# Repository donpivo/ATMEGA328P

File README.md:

Project description:
https://retronics.no/2023/04/09/diy-atmega328p-au-bootloader-burner/
https://retronics.no/2023/04/26/dyi-a-mini-arduino-which-can-power-your-peripherals/

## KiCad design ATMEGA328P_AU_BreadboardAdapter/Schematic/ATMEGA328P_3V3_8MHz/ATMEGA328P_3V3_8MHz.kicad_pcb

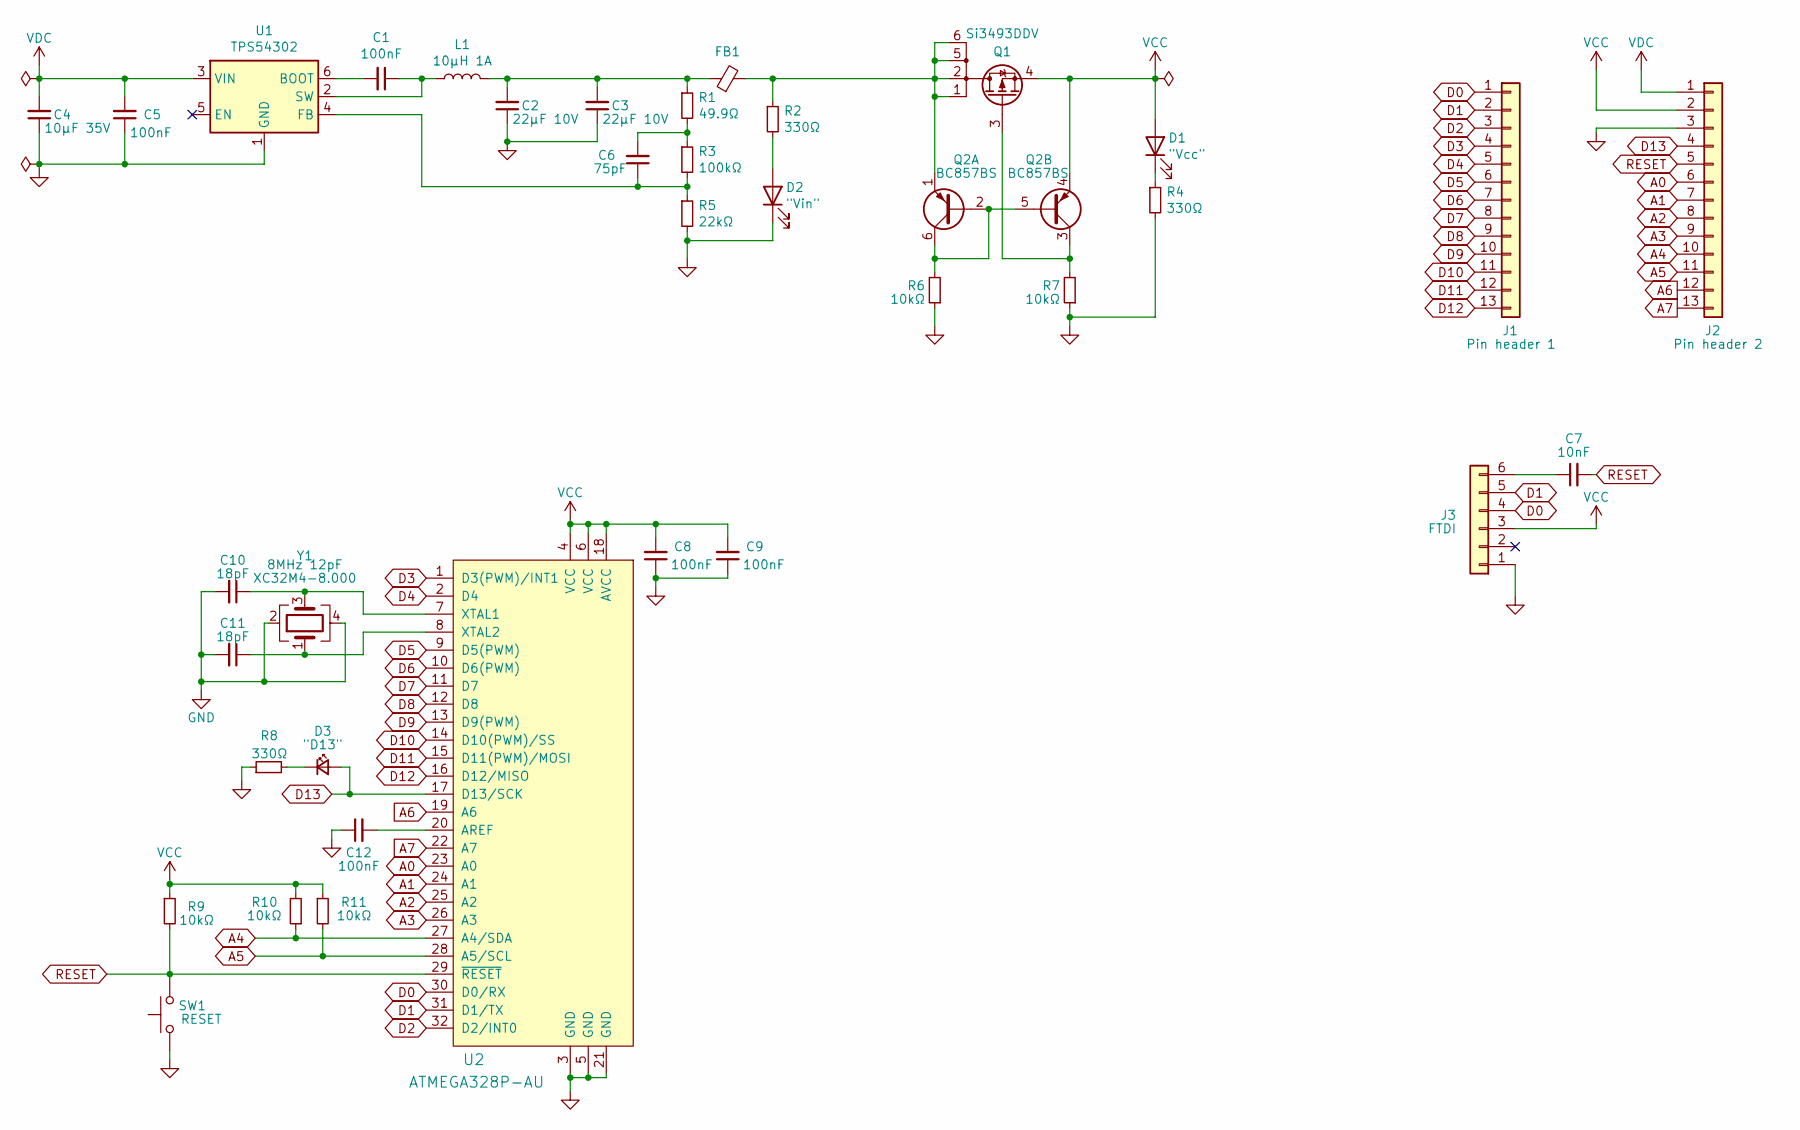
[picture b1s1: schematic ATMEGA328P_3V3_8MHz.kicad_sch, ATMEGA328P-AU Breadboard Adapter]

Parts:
C1, C5, C8, C9, C12: 100nF; C_0603_1608Metric_Pad1.08x0.95mm_HandSolder
C2, C3: 22µF 10V; C_0603_1608Metric_Pad1.08x0.95mm_HandSolder
C4: 10µF 35V; C_0603_1608Metric_Pad1.08x0.95mm_HandSolder
C6: 75pF; C_0603_1608Metric_Pad1.08x0.95mm_HandSolder
C7: 10nF; C_0603_1608Metric_Pad1.08x0.95mm_HandSolder
C10, C11: 18pF; C_0603_1608Metric_Pad1.08x0.95mm_HandSolder
D1: "Vcc"; LED_0603_1608Metric_Pad1.05x0.95mm_HandSolder
D2: "Vin"; LED_0603_1608Metric_Pad1.05x0.95mm_HandSolder
D3: "D13"; LED_0603_1608Metric_Pad1.05x0.95mm_HandSolder
FB1: FerriteBead_Small; L_0603_1608Metric_Pad1.05x0.95mm_HandSolder
J1: Pin header 1; PinHeader_1x13_P2.54mm_Vertical
J2: Pin header 2; PinHeader_1x13_P2.54mm_Vertical
J3: FTDI; PinHeader_1x06_P2.54mm_Vertical
L1: 10µH 1A; L_Taiyo-Yuden_NR-20xx_HandSoldering
Q1: Si3493DDV; SOT95P280X100-6N
Q2: BC857BS; SOT-363_SC-70-6-Handsoldering
R1: 49.9Ω; R_0603_1608Metric_Pad0.98x0.95mm_HandSolder
R2, R4, R8: 330Ω; R_0603_1608Metric_Pad0.98x0.95mm_HandSolder
R3: 100kΩ; R_0603_1608Metric_Pad0.98x0.95mm_HandSolder
R5: 22kΩ; R_0603_1608Metric_Pad0.98x0.95mm_HandSolder
R6, R7, R9, R10, R11: 10kΩ; R_0603_1608Metric_Pad0.98x0.95mm_HandSolder
SW1: RESET; Tactile_sw_SMD_side_01
U1: TPS54302; SOT-23-6_Handsoldering
U2: ATMEGA328P-AU; TQFP-32_7x7mm
Y1: 8MHz 12pF; Crystal_SMD_SeikoEpson_TSX3225-4Pin_3.2x2.5mm_HandSoldering

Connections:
A0: J2.6, U2.23 (A0)
A1: J2.7, U2.24 (A1)
A2: J2.8, U2.25 (A2)
A3: J2.9, U2.26 (A3)
A4: J2.10, R10.1, U2.27 (A4/SDA)
A5: J2.11, R11.2, U2.28 (A5/SCL)
A6: J2.12, U2.19 (A6)
A7: J2.13, U2.22 (A7)
D0: J1.1, J3.4, U2.30 (D0/RX)
D1: J1.2, J3.5, U2.31 (D1/TX)
D2: J1.3, U2.32 (D2/INT0)
D3: J1.4, U2.1 (D3(PWM)/INT1)
D4: J1.5, U2.2 (D4)
D5: J1.6, U2.9 (D5(PWM))
D6: J1.7, U2.10 (D6(PWM))
D7: J1.8, U2.11 (D7)
D8: J1.9, U2.12 (D8)
D9: J1.10, U2.13 (D9(PWM))
D10: J1.11, U2.14 (D10(PWM)/SS)
D11: J1.12, U2.15 (D11(PWM)/MOSI)
D12: J1.13, U2.16 (D12/MISO)
D13: D3.2 (A), J2.4, U2.17 (D13/SCK)
unnamed: C1.1, L1.1, U1.2 (SW)
unnamed: C1.2, U1.6 (BOOT)
unnamed: C2.2, C3.2, FB1.1, L1.2, R1.1
unnamed: C6.1, R3.2, R5.1, U1.4 (FB)
unnamed: C6.2, R1.2, R3.1
unnamed: C7.1, J3.6
unnamed: C10.1, U2.7 (XTAL1), Y1.3
unnamed: C11.1, U2.8 (XTAL2), Y1.1
unnamed: C12.2, U2.20 (AREF)
unnamed: D1.1 (K), R4.1
unnamed: D2.2 (A), R2.2
unnamed: D3.1 (K), R8.2
unnamed: FB1.2, Q1.1 (D), Q1.2 (D), Q1.5 (D), Q1.6 (D), Q2.1 (E1), R2.1
unnamed: Q1.3 (G), Q2.3 (C2), R7.2
unnamed: Q2.2 (B1), Q2.5 (B2), Q2.6 (C1), R6.2
RESET: C7.2, J2.5, R9.2, SW1.2, U2.29 (~RESET)
VCC: C8.2, C9.2, D1.2 (A), J2.2, J3.3, Q1.4 (S), Q2.4 (E2), R9.1, R10.2, R11.1, U2.4 (VCC), U2.6 (VCC), U2.18 (AVCC)
VDC: C4.2, C5.2, J2.1, U1.3 (VIN)

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
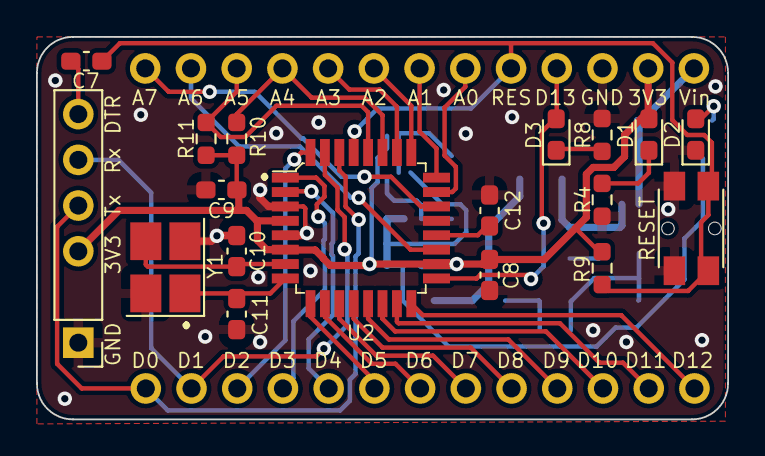
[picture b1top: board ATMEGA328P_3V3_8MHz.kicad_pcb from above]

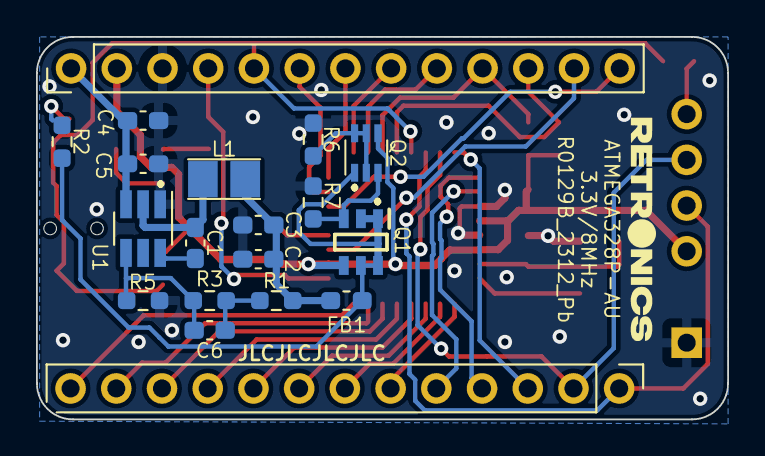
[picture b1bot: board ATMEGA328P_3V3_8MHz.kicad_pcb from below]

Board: 2 copper layers, 38.4 x 21.2 mm, 37 parts (19 on the bottom side), 41 nets.

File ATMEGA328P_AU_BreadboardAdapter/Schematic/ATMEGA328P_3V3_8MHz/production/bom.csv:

Designator,Footprint,Quantity,Value,LCSC Part #
"C1, C12, C5, C8, C9",0603,5,100nF,
"C10, C11",0603,2,22pF,
"C2, C3",0603,2,22µF 10V,
C4,0603,1,10µF 35V,
C6,0603,1,75pF,
C7,0603,1,10nF,
D1,0603,1,"""Vcc""",
D2,0603,1,"""Vin""",
D3,0603,1,"""D13""",
FB1,0603,1,FerriteBead_Small,
J1,PinHeader_1x13_P2.54mm_Vertical,1,Pin header 1,
J2,PinHeader_1x13_P2.54mm_Vertical,1,Pin header 2,
J3,PinHeader_1x06_P2.54mm_Vertical,1,FTDI,
L1,L_Taiyo-Yuden_NR-20xx_HandSoldering,1,10µH 1A,
Q1,SOT95P280X100-6N,1,Si3493DDV,
Q2,SOT-363_SC-70-6-Handsoldering,1,BC857BS,
R1,0603,1,49.9Ω,
"R10, R11, R6, R7, R9",0603,5,10kΩ,
"R2, R4, R8",0603,3,560Ω,
R3,0603,1,100kΩ,
R5,0603,1,13.3kΩ,
SW1,Tactile_sw_SMD_side_01,1,RESET,
U1,SOT-23-6_Handsoldering,1,TPS54302,
U2,TQFP-32_7x7mm,1,ATMEGA328P-AU,
Y1,Crystal_SMD_SeikoEpson_TSX3225-4Pin_3.2x2.5mm_HandSoldering,1,16MHz 16pF,

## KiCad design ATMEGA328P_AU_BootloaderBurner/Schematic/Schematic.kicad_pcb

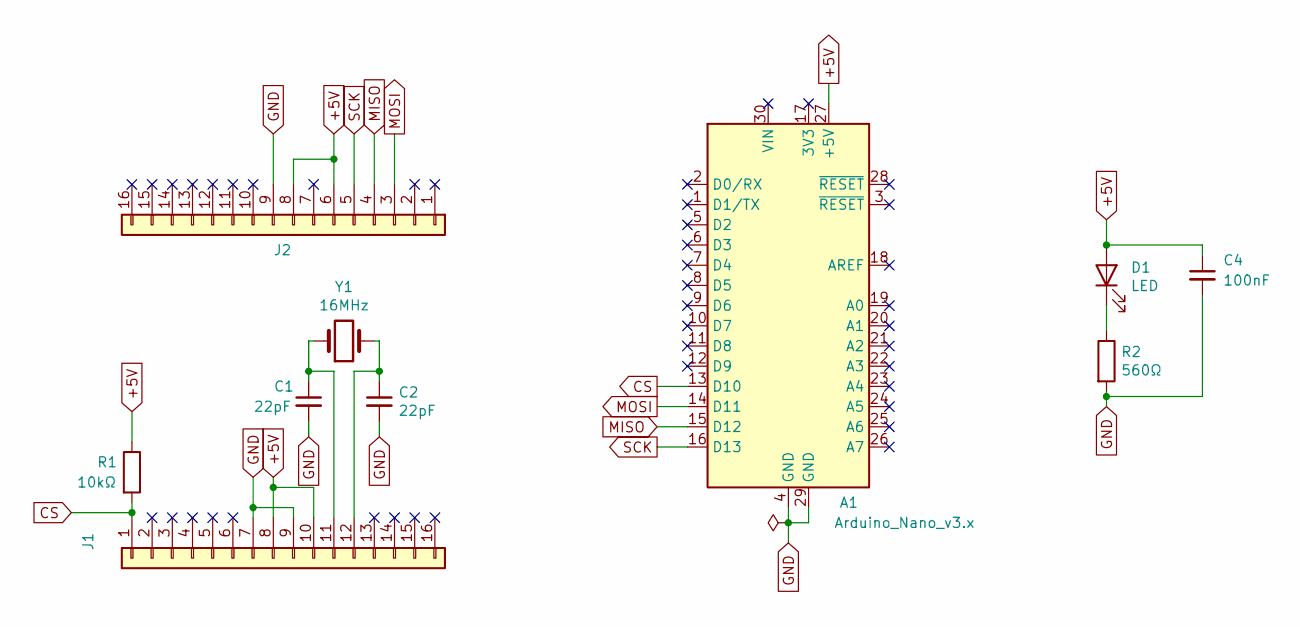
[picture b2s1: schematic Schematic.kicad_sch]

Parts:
A1: Arduino_Nano_v3.x; Arduino_Nano
C1, C2: 22pF; C_0805_2012Metric_Pad1.18x1.45mm_HandSolder
C4: 100nF; C_0805_2012Metric_Pad1.18x1.45mm_HandSolder
D1: LED; LED_0805_2012Metric_Pad1.15x1.40mm_HandSolder
J1, J2: Conn_01x16; PinSocket_1x16_P2.54mm_Vertical
R1: 10kΩ; R_0805_2012Metric_Pad1.20x1.40mm_HandSolder
R2: 560Ω; R_0805_2012Metric_Pad1.20x1.40mm_HandSolder
Y1: 16MHz; Crystal_SMD_HC49-SD

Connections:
+5V: A1.27 (+5V), C4.1, D1.2 (A), J1.8, J1.10, J2.6, J2.8, R1.1
CS: A1.13 (D10), J1.1, R1.2
GND: A1.4 (GND), A1.29 (GND), C1.2, C2.2, C4.2, J1.7, J1.9, J2.9, R2.2
MISO: A1.15 (D12), J2.4
MOSI: A1.14 (D11), J2.3
unnamed: C1.1, J1.11, Y1.1
unnamed: C2.1, J1.12, Y1.2
unnamed: D1.1 (K), R2.1
SCK: A1.16 (D13), J2.5

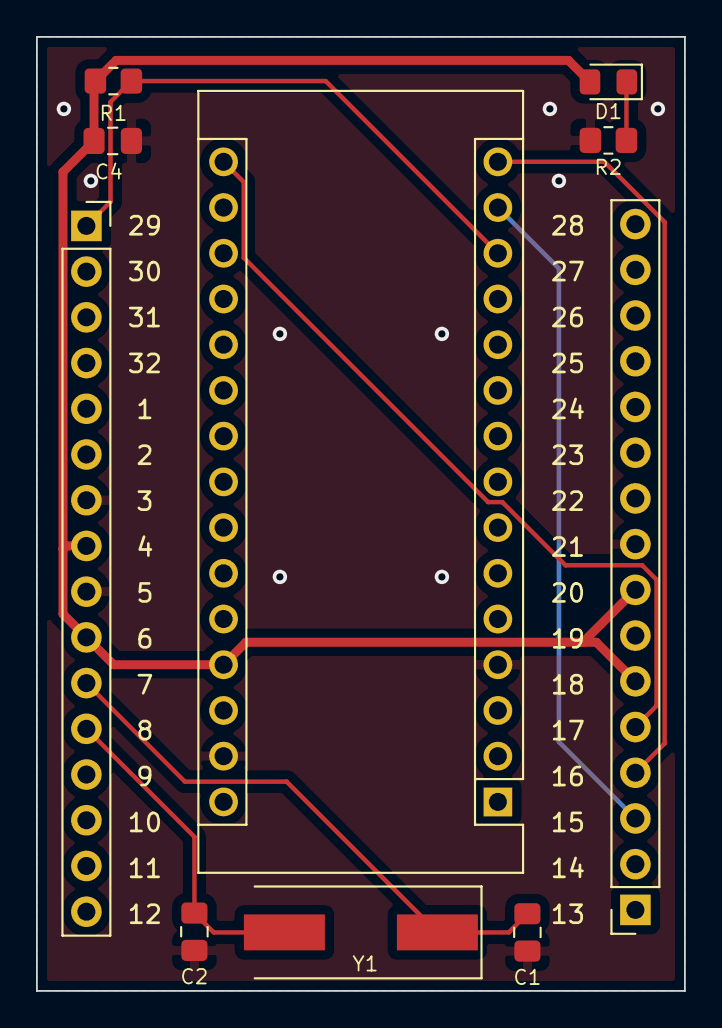
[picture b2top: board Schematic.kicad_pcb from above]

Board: 2 copper layers, 36.0 x 53.0 mm, 10 parts (0 on the bottom side), 9 nets.

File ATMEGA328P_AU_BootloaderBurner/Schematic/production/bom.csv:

Designator,Footprint,Quantity,Value,LCSC Part #
A1,Arduino_Nano,1,Arduino_Nano_v3.x,
"C1, C2",0805,2,22pF,
C4,0805,1,100nF,
D1,0805,1,LED,
"J1, J2",PinSocket_1x16_P2.54mm_Vertical,2,Conn_01x16,
R1,0805,1,10kΩ,
R2,0805,1,560Ω,
Y1,Crystal_SMD_HC49-SD,1,16MHz,

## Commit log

2023-03-04 LDO replaced by buck regulator
2023-04-13 Updated component values. Minor silkscreen changes.
2023-04-13 Removed images
2023-04-13 File cleanup
2023-04-18 Updated production files
2023-05-01 Organized schematic
